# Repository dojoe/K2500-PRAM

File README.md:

# K2500 P/RAM
A P/RAM extension remake for Kurzweil K2500 synthesizers

## Why?

Because people are demanding upwards of 100<span>$</span> on eBay for a part that is simple to make and costs about 20<span>$</span>.

## How?

It's basically just a 1MB SRAM board in a 512Kx16 configuration. The original board had eight 128Kx8 SRAMs and some address decoders, 
but thanks to modern technology we don't need that level of complexity as we can just tack two 512Kx8 SRAMs together.
With that, the only tricky part is to get all those wires routed while keeping a low card profile, which is what I did.

## Compatibility

We tested this in a K2500 and it works like a charm. It also works if you have a KDFX installed, it'll fit nicely next to the KDFX board and won't clash with it.

This will _only_ work in a K2500. It is __not compatible__ with the K2000 or the K2600, these both need completely different boards.

And of course I will assume no responsibility for any problems or damage that may arise from you making your own P/RAM from this design and trying it in a synth. Duh ;)

## The board

This repository contains the KiCAD schematics and board file for the P/RAM extension. There's also a zip file with Gerbers
so you can jump right to ordering a board for yourself, or you simply order from OSHPark directly:

<a href="https://oshpark.com/shared_projects/QDHfglRW"></img></a>

## Parts

The board is built around the AS6C4008, a 5V SRAM chip from Alliance Memory. There may be other pin and voltage compatible parts
out there, but the AS6C4008 is cheap and works. Here's the full BOM, almost too boring to print:

| Designator | Description                       | Digikey part#      | Mouser part#              |
|------------|-----------------------------------|--------------------|---------------------------|
| U1, U2     | Alliance Memory AS6C4008-55ZIN    | 1450-1031-ND       | 913-AS6C4008-55ZIN        |
| J1         | Precision pin header, 45pos, 0.1" | e.g. 1212-1176-ND  | e.g. 437-8008006410001101 |
| C1, C2     | Ceramic Cap X7R 0603 100nF        | ehh                | whatevs                   |
| C3, C4     | Ceramic Cap X7R 0805 1uF          | go find it         | anything goes             |

The trickiest part is probably J1 - you need a pin header with __round pins__, not the usual square ones.
Unfortunately these guys are expensive, but not prohibitively so.

## Assembly and installation

Solder everything up, pin header last. You need to mount the header so that the pins are in the same plane as the board, so you either need right-angle headers, or you mount the pin header flat onto the pads for an SMD-like connection. In the end the PRAM board should stand upright on the K2500 mainboard:

Install the card such that pin 1 (numbered and marked by a notch in the card) points towards the closest edge of the mainboard and the memory chips are facing the memory chips on the mainboard -- see the picture above.

The socket inside the K2500 has very tight tolerances, and the pins tend to move during soldering,
so in the end we had to push on the PRAM card really hard for it to properly sit in the socket.
If you can afford taking the processor board out of the K2500, I recommend plugging the pin header into the socket first,
and then soldering the PRAM board to the pin header while it's in the socket. That will keep the pins aligned during
soldering.

Note that the suggested part number for J1 (1212-1176-ND) has pins that are different thicknesses on either end, and the K2500's
PRAM socket is very tight. The pin header has to be soldered on "upside down" - i.e.: with the longer, thicker sides of the pins
soldered to the PRAM board, and the shorter, thinner sides of the pins used to insert into the socket.

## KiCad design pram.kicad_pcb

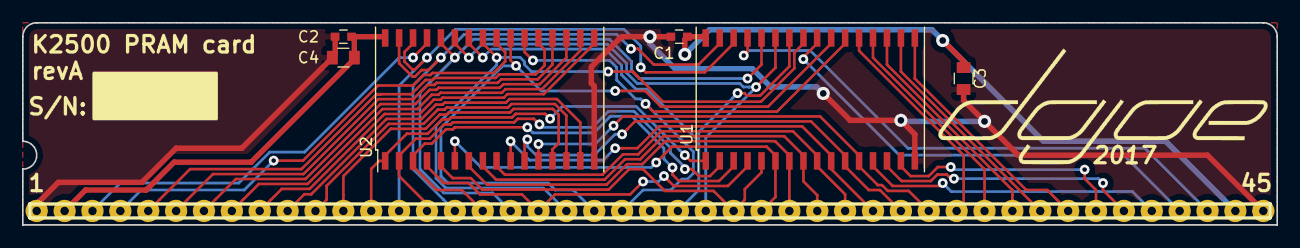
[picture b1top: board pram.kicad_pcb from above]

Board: 4 copper layers, 114.3 x 18.4 mm, 8 parts (0 on the bottom side), 42 nets.

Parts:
C1, C2: 100n; C_0603
C3, C4: 1u; C_0805
J1: K2500-PRAM-CONN; PRAMCONN
U1, U2: AS6C4008-55ZIN; TSOP-II-32_21.0x10.2mm_Pitch1.27mm
VAL: REF; dojoe

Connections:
+5V: C1.1, C2.1, C3.1, C4.1, J1.2, J1.44, U1.32, U2.32
/A0: J1.33, U1.12, U2.12
/A1: J1.32, U1.11, U2.11
/A2: J1.31, U1.10, U2.10
/A3: J1.30, U1.9, U2.9
/A4: J1.29, U1.8, U2.8
/A5: J1.28, U1.7, U2.7
/A6: J1.27, U1.6, U2.6
/A7: J1.26, U1.5, U2.5
/A8: J1.25, U1.27, U2.27
/A9: J1.24, U1.26, U2.26
/A10: J1.21, U1.23, U2.23
/A11: J1.20, U1.25, U2.25
/A12: J1.19, U1.4, U2.4
/A13: J1.18, U1.28, U2.28
/A14: J1.17, U1.3, U2.3
/A15: J1.16, U1.31, U2.31
/A16: J1.15, U1.2, U2.2
/A17: J1.14, U1.30, U2.30
/A18: J1.13, U1.1, U2.1
/CE#: J1.22, U1.22, U2.22
/D0: J1.41, U1.13
/D1: J1.40, U1.14
/D2: J1.39, U1.15
/D3: J1.38, U1.17
/D4: J1.37, U1.18
/D5: J1.36, U1.19
/D6: J1.35, U1.20
/D7: J1.34, U1.21
/D8: J1.12, U2.13
/D9: J1.11, U2.14
/D10: J1.10, U2.15
/D11: J1.9, U2.17
/D12: J1.8, U2.18
/D13: J1.7, U2.19
/D14: J1.6, U2.20
/D15: J1.5, U2.21
/OEHI#: J1.4, U2.24
/OELO#: J1.42, U1.24
/WEHI#: J1.3, U2.29
/WELO#: J1.43, U1.29
GND: C1.2, C2.2, C3.2, C4.2, J1.1, J1.45, U1.16, U2.16

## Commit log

2018-10-07 Full release
2019-05-08 Fix Digikey part number for pin headers
    I accidentally put the part number for 2mm pitch headers here.
    Fixed now. The Mouser part number has been correct from the start.
2019-05-08 Update documentation
2022-06-22 No, GitHub, this is not suddenly a Math expression
